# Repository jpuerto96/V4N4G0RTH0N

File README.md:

# V4N4AG0RTH0N

DISCLAIMER: USE/ORDER AT YOUR OWN RISK I DO NOT GUARANTEE THAT THESE FILES WILL WORK.

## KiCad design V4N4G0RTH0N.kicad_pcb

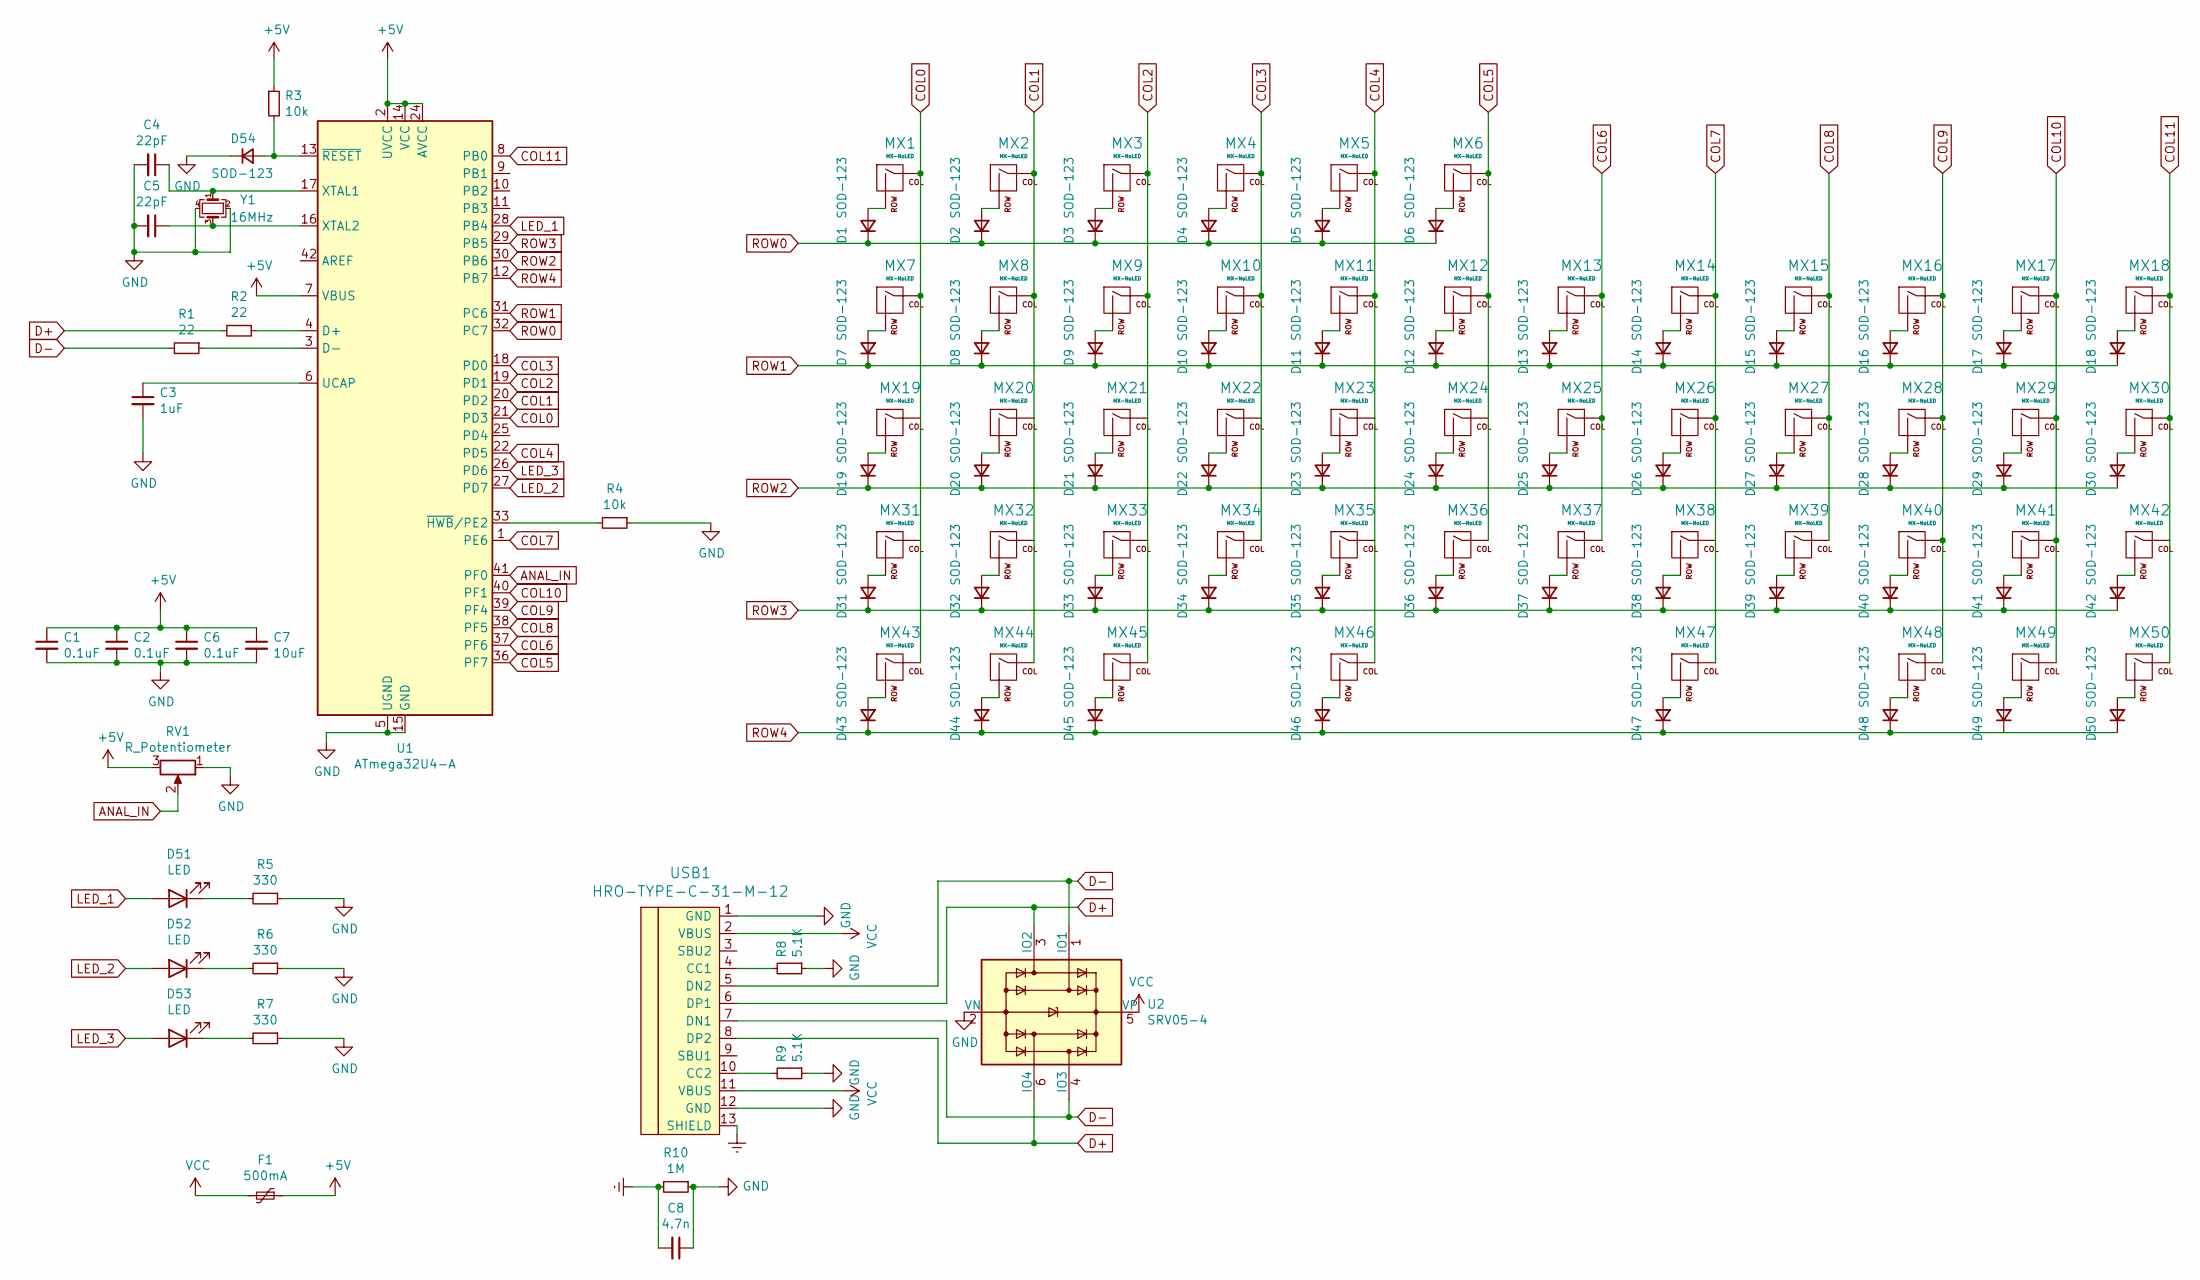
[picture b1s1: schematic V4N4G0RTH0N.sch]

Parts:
C1, C2, C6: 0.1uF; C_0805_2012Metric
C3: 1uF; C_0805_2012Metric
C4, C5: 22pF; C_0805_2012Metric
C7: 10uF; C_0805_2012Metric
C8: 4.7n; C_0805_2012Metric
D1, D2, D3, D4, D5, D6, D7, D8, D9, D10, D11, D12, D13, D14, D15, D16, D17, D18, D19, D20, D21, D22, D23, D24, D25, D26, D27, D28, D29, D30, D31, D32, D33, D34, D35, D36, D37, D38, D39, D40, D41, D42, D43, D44, D45, D46, D47, D48, D49, D50, D54: SOD-123; D_SOD-123
D51, D52, D53: LED; LED_D3.0mm
F1: 500mA; Fuse_0805_2012Metric
MX1, MX2, MX3, MX4, MX5, MX6, MX7, MX8, MX9, MX10, MX11, MX12, MX13, MX14, MX15, MX16, MX17, MX18, MX19, MX20, MX21, MX22, MX23, MX24, MX25, MX26, MX27, MX28, MX29, MX30, MX31, MX32, MX33, MX34, MX35, MX36, MX37, MX38, MX39, MX40, MX41, MX42, MX43, MX44, MX45, MX48, MX49, MX50: MX-NoLED; MX-1U-NoLED
MX46, MX47: MX-NoLED; MX-3U-ReversedStabilizers-NoLED
R1, R2: 22; R_0805_2012Metric
R3, R4: 10k; R_0805_2012Metric
R5, R6, R7: 330; R_0805_2012Metric
R8, R9: 5.1K; R_0805_2012Metric
R10: 1M; R_0805_2012Metric
RV1: R_Potentiometer; Potentiometer_Bourns_PTA3043_Single_Slide
U1: ATmega32U4-A; TQFP-44_10x10mm_P0.8mm
U2: SRV05-4; SOT-23-6
USB1: HRO-TYPE-C-31-M-12
Y1: 16MHz; Crystal_SMD_3225-4Pin_3.2x2.5mm

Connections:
+5V: C1.1, C2.1, C6.1, C7.1, F1.1, R3.1, RV1.3, U1.2 (UVCC), U1.7 (VBUS), U1.14 (VCC), U1.24 (AVCC), U1.34 (VCC), U1.44 (AVCC)
ANAL_IN: RV1.2, U1.41 (PF0)
COL0: MX1.1 (COL), MX7.1 (COL), MX19.1 (COL), MX31.1 (COL), MX43.1 (COL), U1.21 (PD3)
COL1: MX2.1 (COL), MX8.1 (COL), MX20.1 (COL), MX32.1 (COL), MX44.1 (COL), U1.20 (PD2)
COL2: MX3.1 (COL), MX9.1 (COL), MX21.1 (COL), MX33.1 (COL), MX45.1 (COL), U1.19 (PD1)
COL3: MX4.1 (COL), MX10.1 (COL), MX22.1 (COL), MX34.1 (COL), U1.18 (PD0)
COL4: MX5.1 (COL), MX11.1 (COL), MX23.1 (COL), MX35.1 (COL), MX46.1 (COL), U1.22 (PD5)
COL5: MX6.1 (COL), MX12.1 (COL), MX24.1 (COL), MX36.1 (COL), U1.36 (PF7)
COL6: MX13.1 (COL), MX25.1 (COL), MX37.1 (COL), U1.37 (PF6)
COL7: MX14.1 (COL), MX26.1 (COL), MX38.1 (COL), MX47.1 (COL), U1.1 (PE6)
COL8: MX15.1 (COL), MX27.1 (COL), MX39.1 (COL), U1.38 (PF5)
COL9: MX16.1 (COL), MX28.1 (COL), MX40.1 (COL), MX48.1 (COL), U1.39 (PF4)
COL10: MX17.1 (COL), MX29.1 (COL), MX41.1 (COL), MX49.1 (COL), U1.40 (PF1)
COL11: MX18.1 (COL), MX30.1 (COL), MX42.1 (COL), MX50.1 (COL), U1.8 (PB0)
D+: R2.2, U2.3 (IO2), U2.6 (IO4), USB1.6 (DP1), USB1.8 (DP2)
D-: R1.2, U2.1 (IO1), U2.4 (IO3), USB1.5 (DN2), USB1.7 (DN1)
Earth: C8.2, R10.2, USB1.13 (SHIELD)
GND: C1.2, C2.2, C3.2, C4.2, C5.2, C6.2, C7.2, C8.1, D54.1 (K), R4.1, R5.1, R6.1, R7.1, R8.1, R9.1, R10.1, RV1.1, U1.5 (UGND), U1.15 (GND), U1.23 (GND), U1.35 (GND), U1.43 (GND), U2.2 (VN), USB1.1 (GND), USB1.12 (GND), Y1.2, Y1.4
LED_1: D51.2 (A), U1.28 (PB4)
LED_2: D52.2 (A), U1.27 (PD7)
LED_3: D53.2 (A), U1.26 (PD6)
unnamed: C3.1, U1.6 (UCAP)
unnamed: C4.1, U1.17 (XTAL1), Y1.1
unnamed: C5.1, U1.16 (XTAL2), Y1.3
unnamed: D1.2 (A), MX1.2 (ROW)
unnamed: D2.2 (A), MX2.2 (ROW)
unnamed: D3.2 (A), MX3.2 (ROW)
unnamed: D4.2 (A), MX4.2 (ROW)
unnamed: D5.2 (A), MX5.2 (ROW)
unnamed: D6.2 (A), MX6.2 (ROW)
unnamed: D7.2 (A), MX7.2 (ROW)
unnamed: D8.2 (A), MX8.2 (ROW)
unnamed: D9.2 (A), MX9.2 (ROW)
unnamed: D10.2 (A), MX10.2 (ROW)
unnamed: D11.2 (A), MX11.2 (ROW)
unnamed: D12.2 (A), MX12.2 (ROW)
unnamed: D13.2 (A), MX13.2 (ROW)
unnamed: D14.2 (A), MX14.2 (ROW)
unnamed: D15.2 (A), MX15.2 (ROW)
unnamed: D16.2 (A), MX16.2 (ROW)
unnamed: D17.2 (A), MX17.2 (ROW)
unnamed: D18.2 (A), MX18.2 (ROW)
unnamed: D19.2 (A), MX19.2 (ROW)
unnamed: D20.2 (A), MX20.2 (ROW)
unnamed: D21.2 (A), MX21.2 (ROW)
unnamed: D22.2 (A), MX22.2 (ROW)
unnamed: D23.2 (A), MX23.2 (ROW)
unnamed: D24.2 (A), MX24.2 (ROW)
unnamed: D25.2 (A), MX25.2 (ROW)
unnamed: D26.2 (A), MX26.2 (ROW)
unnamed: D27.2 (A), MX27.2 (ROW)
unnamed: D28.2 (A), MX28.2 (ROW)
unnamed: D29.2 (A), MX29.2 (ROW)
unnamed: D30.2 (A), MX30.2 (ROW)
unnamed: D31.2 (A), MX31.2 (ROW)
unnamed: D32.2 (A), MX32.2 (ROW)
unnamed: D33.2 (A), MX33.2 (ROW)
unnamed: D34.2 (A), MX34.2 (ROW)
unnamed: D35.2 (A), MX35.2 (ROW)
unnamed: D36.2 (A), MX36.2 (ROW)
unnamed: D37.2 (A), MX37.2 (ROW)
unnamed: D38.2 (A), MX38.2 (ROW)
unnamed: D39.2 (A), MX39.2 (ROW)
unnamed: D40.2 (A), MX40.2 (ROW)
unnamed: D41.2 (A), MX41.2 (ROW)
unnamed: D42.2 (A), MX42.2 (ROW)
unnamed: D43.2 (A), MX43.2 (ROW)
unnamed: D44.2 (A), MX44.2 (ROW)
unnamed: D45.2 (A), MX45.2 (ROW)
unnamed: D46.2 (A), MX46.2 (ROW)
unnamed: D47.2 (A), MX47.2 (ROW)
unnamed: D48.2 (A), MX48.2 (ROW)
unnamed: D49.2 (A), MX49.2 (ROW)
unnamed: D50.2 (A), MX50.2 (ROW)
unnamed: D51.1 (K), R5.2
unnamed: D52.1 (K), R6.2
unnamed: D53.1 (K), R7.2
unnamed: D54.2 (A), R3.2, U1.13 (~RESET)
unnamed: R1.1, U1.3 (D-)
unnamed: R2.1, U1.4 (D+)
unnamed: R4.2, U1.33 (~HWB~/PE2)
unnamed: R8.2, USB1.4 (CC1)
unnamed: R9.2, USB1.10 (CC2)
ROW0: D1.1 (K), D2.1 (K), D3.1 (K), D4.1 (K), D5.1 (K), D6.1 (K), U1.32 (PC7)
ROW1: D7.1 (K), D8.1 (K), D9.1 (K), D10.1 (K), D11.1 (K), D12.1 (K), D13.1 (K), D14.1 (K), D15.1 (K), D16.1 (K), D17.1 (K), D18.1 (K), U1.31 (PC6)
ROW2: D19.1 (K), D20.1 (K), D21.1 (K), D22.1 (K), D23.1 (K), D24.1 (K), D25.1 (K), D26.1 (K), D27.1 (K), D28.1 (K), D29.1 (K), D30.1 (K), U1.30 (PB6)
ROW3: D31.1 (K), D32.1 (K), D33.1 (K), D34.1 (K), D35.1 (K), D36.1 (K), D37.1 (K), D38.1 (K), D39.1 (K), D40.1 (K), D41.1 (K), D42.1 (K), U1.29 (PB5)
ROW4: D43.1 (K), D44.1 (K), D45.1 (K), D46.1 (K), D47.1 (K), D48.1 (K), D49.1 (K), D50.1 (K), U1.12 (PB7)
VCC: F1.2, U2.5 (VP), USB1.2 (VBUS), USB1.11 (VBUS)

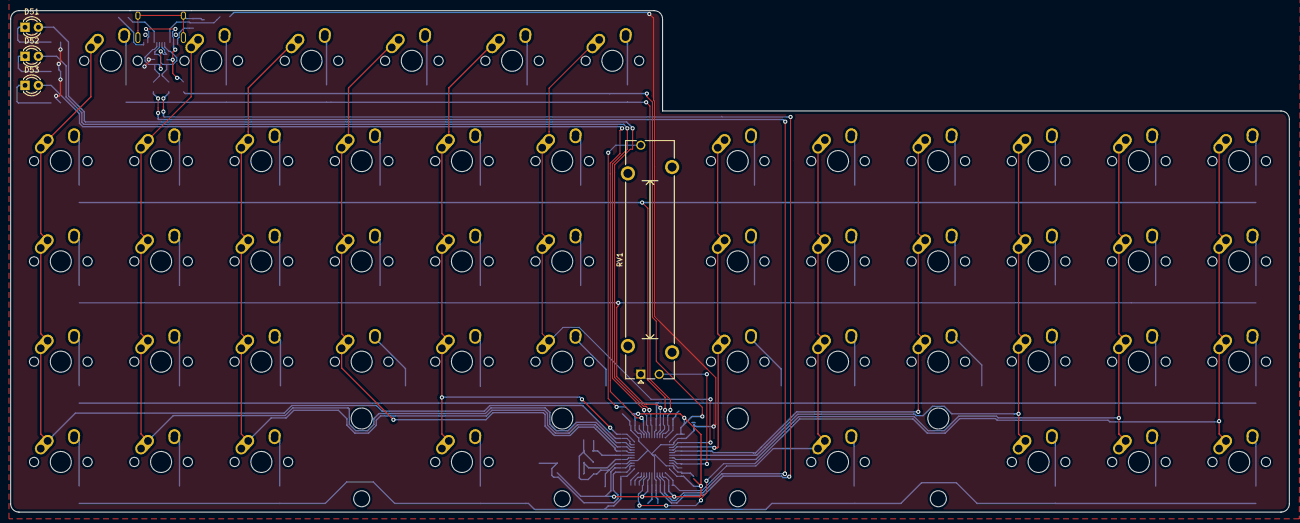
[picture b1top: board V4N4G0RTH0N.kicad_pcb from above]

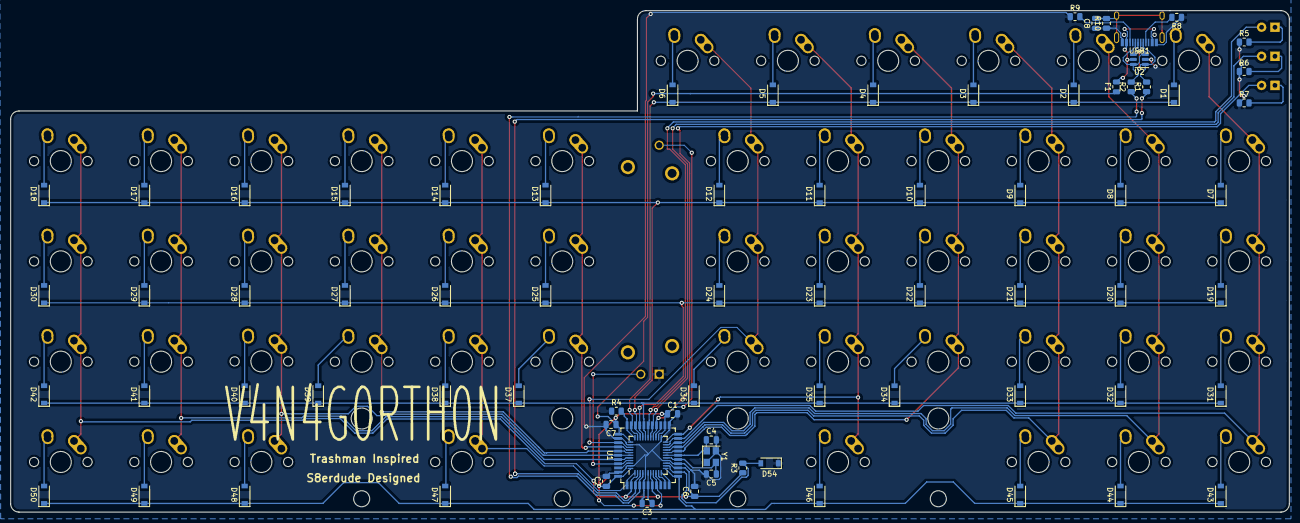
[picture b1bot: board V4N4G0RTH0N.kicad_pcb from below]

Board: 2 copper layers, 242.9 x 95.2 mm, 128 parts (74 on the bottom side), 89 nets.

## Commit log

2020-12-12 Initial commit and git submodule adds
2020-12-12 Add symbol tables
2020-12-12 Add all components
2020-12-12 Basic tutorial done
2020-12-13 Almost done?
2020-12-14 Placed USB-C Components
2020-12-14 change project name bc im a dumb dumb
2020-12-14 remove files
2020-12-14 I think I'm done??
2020-12-15 Rev 1.0
2020-12-15 Add gerbers
2020-12-16 Rev 1.1
2020-12-16 V4N BOM
2020-12-16 0RTH0 GOOD
2021-01-08 V2 sch changes
2021-01-08 Change silk
2021-01-08 Update gerbers and drill files
2021-01-08 More
2021-01-09 Update BOM
2021-01-12 V4N v2
2021-03-12 Add slider
2021-12-07 still need to do some cleanup
2021-12-07 add a STEP
2023-03-24 Update pcb to remove nub for v3 compatibility
2023-03-24 README disclaimer
2023-03-24 Initial .gitignore
2023-03-24 Remove unnecessary things
2023-03-24 Remove outdated .step file
2023-03-24 Add Production files
